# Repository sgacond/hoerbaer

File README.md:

# HörBär

## Idea
Build a more advanced, better sounding and better looking big brother of the commercially available [Hörbert](https://www.hoerbert.com/).

## Components
- A wonderful grand-father home made wooden housing. See: [C. Mosberger Restaurierung und Kunsthandwerk](http://www.cmosberger.ch/).
- MCU: ESP32
- PmodI2S DAC
- Adafruit MAX9744 based amplifier board
- Visaton FX 10 5" coaxial speaker

## Credits
Some of Neil Kolbans [CPP Utils](https://github.com/nkolban/esp32-snippets).  
Ideas and components from [ESP32_MP3_Decoder](https://github.com/MrBuddyCasino/ESP32_MP3_Decoder).  
Thank you!

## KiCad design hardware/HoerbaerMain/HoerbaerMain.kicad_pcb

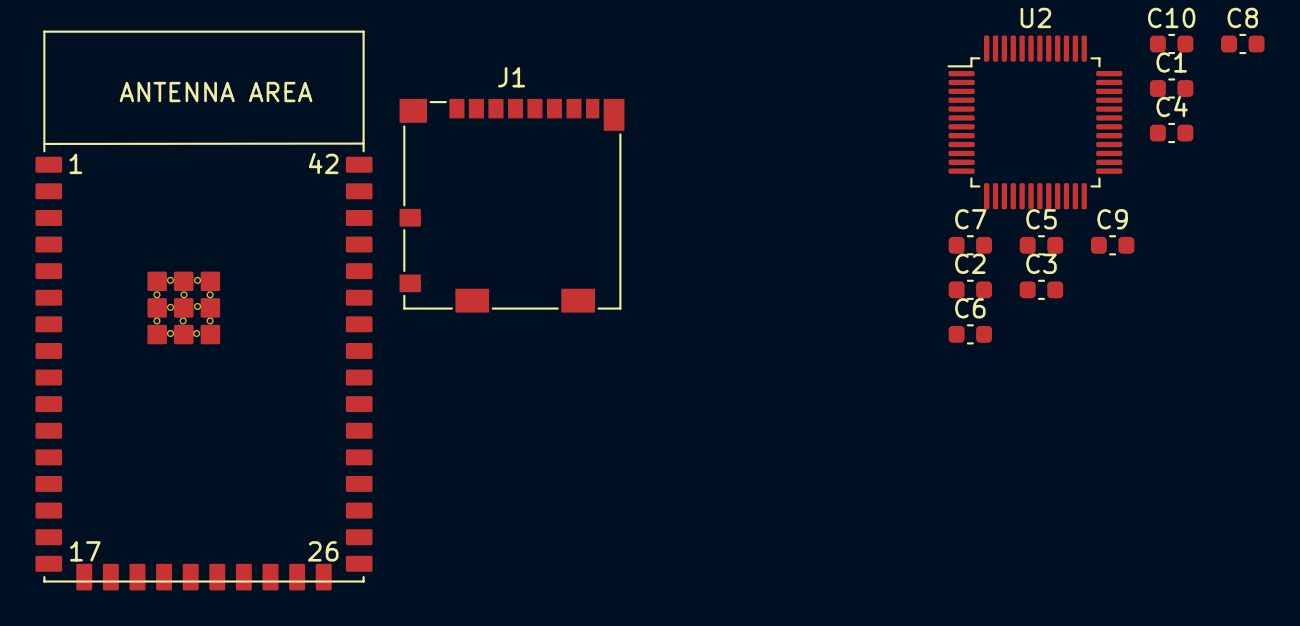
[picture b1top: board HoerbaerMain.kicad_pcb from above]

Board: 2 copper layers, 13 parts (0 on the bottom side), 3 nets, no tracks yet.

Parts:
C1, C2, C3, C4, C5, C6, C7, C8, C9, C10: 100nF; C_0603_1608Metric
J1: Micro_SD_Card; microSD_HC_Molex_104031-0811
U1: esp32-s2-wroom; esp32-s2-wrooom
U2: VS1053B; LQFP-48_7x7mm_P0.5mm

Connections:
GNDA: C1.2, C2.2, C3.2, U2.37 (AGND0), U2.40 (AGND1), U2.41 (AGND2), U2.47 (AGND3)
GNDD: C4.2, C5.2, C6.2, C7.2, C8.2, C9.2, C10.2, U2.4 (DGND0), U2.16 (DGND1), U2.20 (DGND2), U2.21 (DGND3), U2.22 (DGND4), U2.35 (GND)
VCC: C1.1, C2.1, C3.1, C4.1, C5.1, C6.1, C7.1, C8.1, C9.1, C10.1, U2.5 (CVDD0), U2.6 (IOVDD0), U2.7 (CVDD1), U2.14 (IOVDD1), U2.19 (IOVDD2), U2.24 (CVDD2), U2.31 (CVDD3), U2.38 (AVDD0), U2.43 (AVDD1), U2.45 (AVDD2)

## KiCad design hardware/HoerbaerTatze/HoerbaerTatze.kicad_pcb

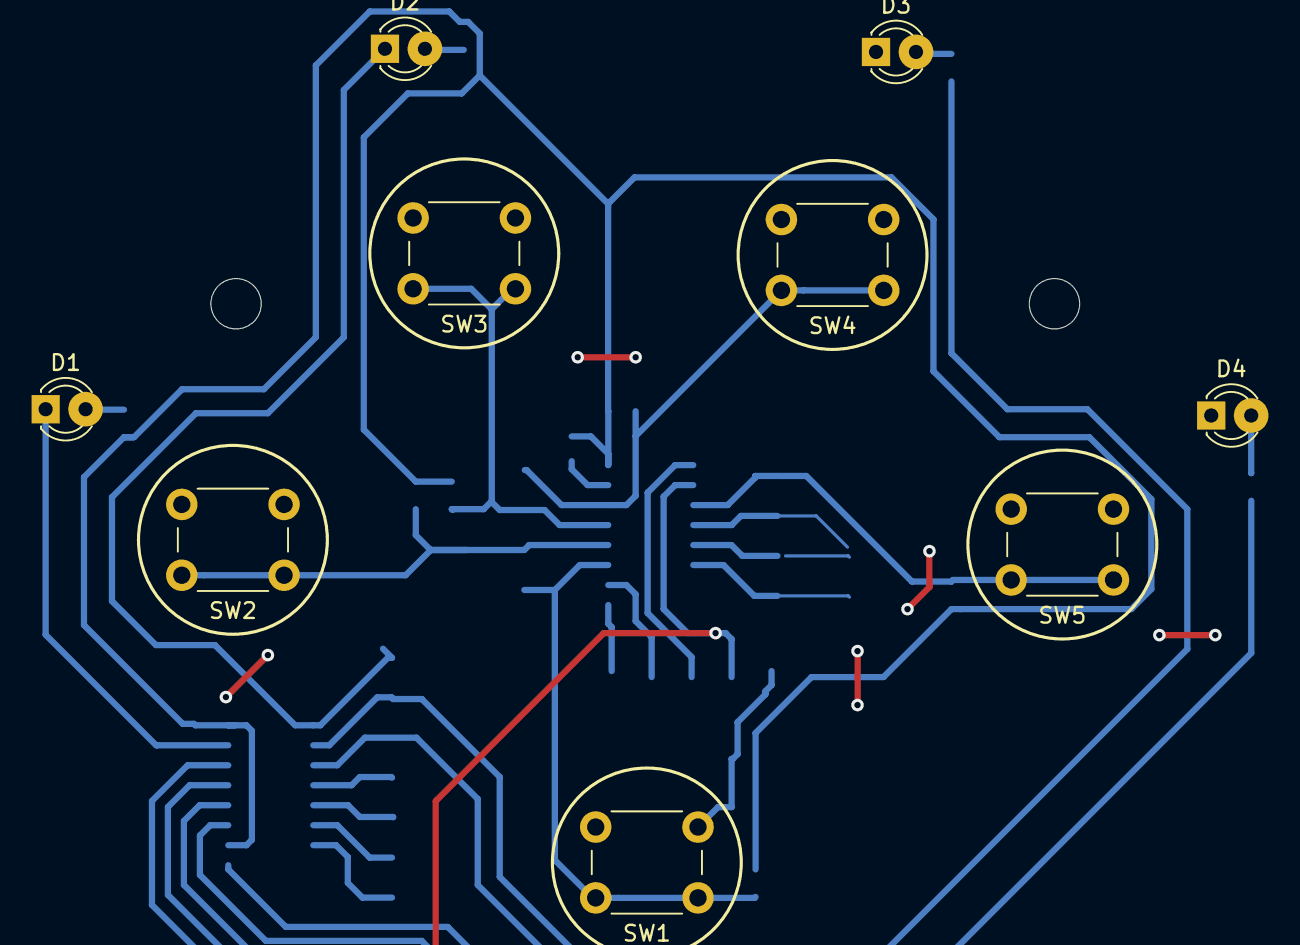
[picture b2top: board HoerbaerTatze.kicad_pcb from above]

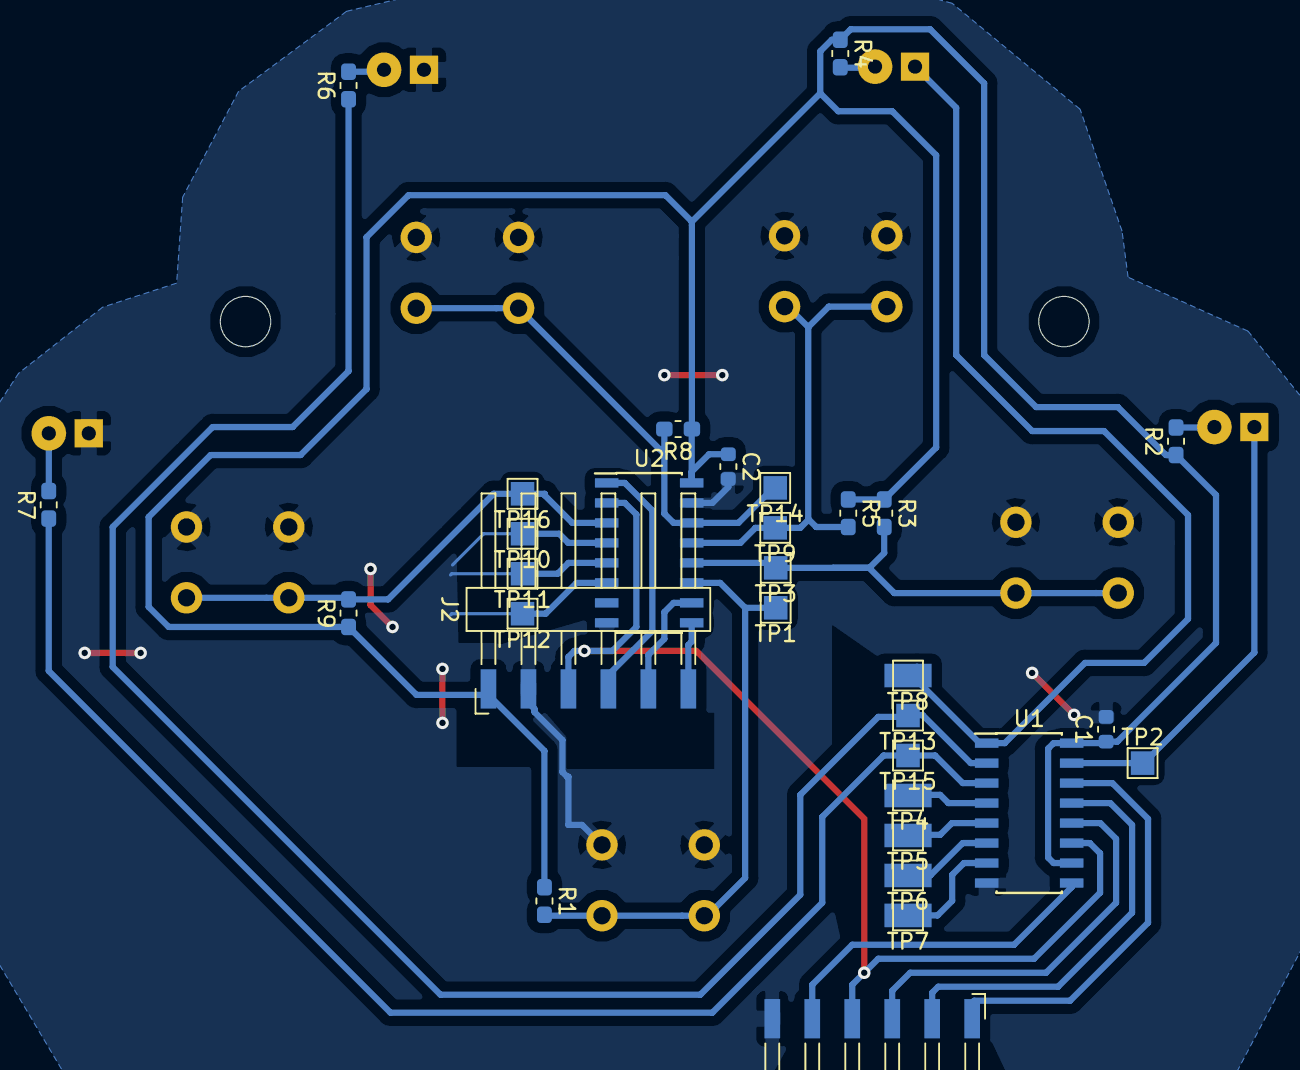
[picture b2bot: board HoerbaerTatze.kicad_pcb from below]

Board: 2 copper layers, 43 parts (31 on the bottom side), 27 nets.

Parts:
C1, C2: C; C_0603_1608Metric
D1, D2, D3, D4: LED; LED_D3.0mm
J1, J2: SWITCH; Harwin_M20-89006xx_1x06_P2.54mm_Horizontal
MH1, MH3, MH4: MountingHole; MountingHole_3.2mm_M3
R1, R3, R5, R8, R9: 10k; R_0603_1608Metric_Pad1.05x0.95mm_HandSolder
R2, R4, R6, R7: R; R_0603_1608Metric_Pad1.05x0.95mm_HandSolder
SW1, SW2, SW3, SW4, SW5: SW_Push; SW_PUSH_6mm
TP1, TP2, TP3, TP4, TP5, TP6, TP7, TP8, TP9, TP10, TP11, TP12, TP13, TP14, TP15, TP16: TestPoint; TestPoint_Pad_1.5x1.5mm
U1: 74HC595; SOIC-16_3.9x9.9mm_P1.27mm
U2: 74HC165; SOIC-16_3.9x9.9mm_P1.27mm

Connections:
CHAIN_SERIAL_IN: J2.5, U2.10
CHAIN_SERIAL_OUT: J1.5, U1.9
CLK: J1.4, J2.3, U1.11, U2.2
GND: C1.2, C2.2, D3.1, D4.1, J1.6, J2.2, SW1.1, SW2.1, SW3.1, SW4.1, SW5.1, TP10.1, TP11.1, TP12.1, U1.8, U2.4, U2.5, U2.6, U2.8, U2.15
IN_LATCH: J2.4, U2.1
LED1_LOW: D1.1, TP2.1, U1.15
LED2_LOW: D2.1, TP8.1, U1.1
LED3_HIGH: R6.1, TP13.1, U1.2
LED4_HIGH: R7.1, TP15.1, U1.3
LED_DIM_PWM: J1.2, U1.13
MISO: J2.6, U2.9
MOSI: J1.1, U1.14
unnamed: D1.2, R2.2
unnamed: D2.2, R4.2
unnamed: D3.2, R6.2
unnamed: D4.2, R7.2
unnamed: TP4.1, U1.4
unnamed: TP5.1, U1.5
unnamed: TP6.1, U1.6
unnamed: TP7.1, U1.7
OUT_LATCH: J1.3, U1.12
SW1: R1.2, SW1.2, TP1.1, U2.11
SW2: R3.2, SW2.2, TP3.1, U2.12
SW3: R5.2, SW3.2, TP9.1, U2.13
SW4: R8.2, SW4.2, TP14.1, U2.14
SW5: R9.2, SW5.2, TP16.1, U2.3
VCC: C1.1, C2.1, J2.1, R1.1, R2.1, R3.1, R4.1, R5.1, R8.1, R9.1, U1.10, U1.16, U2.16

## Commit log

2018-10-20 WIP: audio player.
2018-10-20 WIP: audio player
2018-10-22 Added better dynamic wave header parsing.
2018-10-22 Wip: audio, ...
2018-12-16 wip: firmware, ui prototype and boilerplate
2018-12-16 ignored vscode cpp browse db.
2018-12-18 Bear is talking - nose can adjust volume... Much to do!
2018-12-21 WIP: audio playing.
2018-12-23 WIP: playing, sleeping, pause, resume, ...
2018-12-24 File loading - fs reading, paw events, ...
2018-12-24 Eof -> to next song.
2018-12-26 Some fixes after successful christmas presentation to the client ;).
2018-12-26 GPIO15 amp fix, SPI CS was selected.
2018-12-26 Update readme.
2018-12-26 Added readme - added pictures.
2018-12-26 Updated readme and content.
2018-12-27 Added License and component license files.
2018-12-27 Modified Readme.
2019-07-19 Changed max volume (no technical reason ;))
2020-02-18 ESP_IDF update
2023-06-04 Try v5 update.
2023-06-04 Compilable on v3.3.6
2023-06-04 Released max volume
2025-06-24 Bump pbkdf2 from 3.0.17 to 3.1.3 in /webui
    Bumps [pbkdf2](https://github.com/crypto-browserify/pbkdf2) from 3.0.17 to 3.1.3.
    - [Changelog](https://github.com/browserify/pbkdf2/blob/master/CHANGELOG.md)
    - [Commits](https://github.com/crypto-browserify/pbkdf2/compare/v3.0.17...v3.1.3)
    ---
    updated-dependencies:
    - dependency-name: pbkdf2
2025-07-18 Bump on-headers and compression in /webui
    Bumps [on-headers](https://github.com/jshttp/on-headers) and [compression](https://github.com/expressjs/compression). These dependencies needed to be updated together.
    Updates `on-headers` from 1.0.1 to 1.1.0
    - [Release notes](https://github.com/jshttp/on-headers/releases)
    - [Changelog](https://github.com/jshttp/on-headers/blob/master/HISTORY.md)
    - [Commits](https://github.com/jshttp/on-headers/compare/v1.0.1...v1.1.0)
    Updates `compression` from 1.7.3 to 1.8.1
2025-08-06 Bump tmp and react-scripts in /webui
    Removes [tmp](https://github.com/raszi/node-tmp). It's no longer used after updating ancestor dependency [react-scripts](https://github.com/facebook/create-react-app/tree/HEAD/packages/react-scripts)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
    Removes `tmp`
    Updates `react-scripts` from 2.1.1 to 5.0.1
    - [Release notes](https://github.com/facebook/create-react-app/releases)
    - [Changelog](https://github.com/facebook/create-react-app/blob/main/CHANGELOG-2.x.md)
    - [Commits](https://github.com/facebook/create-react-app/commits/react-scripts@5.0.1/packages/react-scripts)
2025-08-20 Bump brace-expansion from 1.1.11 to 1.1.12 in /webui
    Bumps [brace-expansion](https://github.com/juliangruber/brace-expansion) from 1.1.11 to 1.1.12.
    - [Release notes](https://github.com/juliangruber/brace-expansion/releases)
    - [Commits](https://github.com/juliangruber/brace-expansion/compare/1.1.11...v1.1.12)
    ---
    updated-dependencies:
    - dependency-name: brace-expansion
2025-08-21 Bump cipher-base from 1.0.4 to 1.0.6 in /webui
    Bumps [cipher-base](https://github.com/crypto-browserify/cipher-base) from 1.0.4 to 1.0.6.
    - [Changelog](https://github.com/browserify/cipher-base/blob/master/CHANGELOG.md)
    - [Commits](https://github.com/crypto-browserify/cipher-base/compare/v1.0.4...v1.0.6)
    ---
    updated-dependencies:
    - dependency-name: cipher-base
2025-08-21 Bump sha.js from 2.4.11 to 2.4.12 in /webui
    Bumps [sha.js](https://github.com/crypto-browserify/sha.js) from 2.4.11 to 2.4.12.
    - [Changelog](https://github.com/browserify/sha.js/blob/master/CHANGELOG.md)
    - [Commits](https://github.com/crypto-browserify/sha.js/compare/v2.4.11...v2.4.12)
    ---
    updated-dependencies:
    - dependency-name: sha.js
2025-11-18 Bump js-yaml from 3.12.0 to 3.14.2 in /webui
    Bumps [js-yaml](https://github.com/nodeca/js-yaml) from 3.12.0 to 3.14.2.
    - [Changelog](https://github.com/nodeca/js-yaml/blob/master/CHANGELOG.md)
    - [Commits](https://github.com/nodeca/js-yaml/compare/3.12.0...3.14.2)
    ---
    updated-dependencies:
    - dependency-name: js-yaml
2025-11-27 Bump node-forge and react-scripts in /webui
    Bumps [node-forge](https://github.com/digitalbazaar/forge) to 1.3.2 and updates ancestor dependency [react-scripts](https://github.com/facebook/create-react-app/tree/HEAD/packages/react-scripts). The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
    Updates `node-forge` from 0.7.5 to 1.3.2
    - [Changelog](https://github.com/digitalbazaar/forge/blob/main/CHANGELOG.md)
    - [Commits](https://github.com/digitalbazaar/forge/compare/0.7.5...v1.3.2)
    Updates `react-scripts` from 2.1.1 to 5.0.1
    - [Release notes](https://github.com/facebook/create-react-app/releases)
2026-01-01 Bump qs and react-scripts in /webui
    Bumps [qs](https://github.com/ljharb/qs) to 6.14.1 and updates ancestor dependency [react-scripts](https://github.com/facebook/create-react-app/tree/HEAD/packages/react-scripts). These dependencies n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
    Updates `qs` from 6.5.2 to 6.14.1
    - [Changelog](https://github.com/ljharb/qs/blob/main/CHANGELOG.md)
    - [Commits](https://github.com/ljharb/qs/compare/v6.5.2...v6.14.1)
    Updates `react-scripts` from 2.1.1 to 5.0.1
    - [Release notes](https://github.com/facebook/create-react-app/releases)
2026-01-15 Bump diff and react-scripts in /webui
    Removes [diff](https://github.com/kpdecker/jsdiff). It's no longer used after updating ancestor dependency [react-scripts](https://github.com/facebook/create-react-app/tree/HEAD/packages/react-script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
    Removes `diff`
    Updates `react-scripts` from 2.1.1 to 5.0.1
    - [Release notes](https://github.com/facebook/create-react-app/releases)
    - [Changelog](https://github.com/facebook/create-react-app/blob/main/CHANGELOG-2.x.md)
    - [Commits](https://github.com/facebook/create-react-app/commits/react-scripts@5.0.1/packages/react-scripts)
2026-01-17 Bump tar and react-scripts in /webui
    Removes [tar](https://github.com/isaacs/node-tar). It's no longer used after updating ancestor dependency [react-scripts](https://github.com/facebook/create-react-app/tree/HEAD/packages/react-scripts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
    Removes `tar`
    Updates `react-scripts` from 2.1.1 to 5.0.1
    - [Release notes](https://github.com/facebook/create-react-app/releases)
    - [Changelog](https://github.com/facebook/create-react-app/blob/main/CHANGELOG-2.x.md)
    - [Commits](https://github.com/facebook/create-react-app/commits/react-scripts@5.0.1/packages/react-scripts)
2026-01-24 Bump lodash from 4.17.11 to 4.17.23 in /webui
    Bumps [lodash](https://github.com/lodash/lodash) from 4.17.11 to 4.17.23.
    - [Release notes](https://github.com/lodash/lodash/releases)
    - [Commits](https://github.com/lodash/lodash/compare/4.17.11...4.17.23)
    ---
    updated-dependencies:
    - dependency-name: lodash
2026-01-30 Bump diff from 3.5.0 to 3.5.1 in /webui
    Bumps [diff](https://github.com/kpdecker/jsdiff) from 3.5.0 to 3.5.1.
    - [Changelog](https://github.com/kpdecker/jsdiff/blob/master/release-notes.md)
    - [Commits](https://github.com/kpdecker/jsdiff/compare/v3.5.0...v3.5.1)
    ---
    updated-dependencies:
    - dependency-name: diff
2026-02-03 Bump url-parse from 1.4.4 to 1.5.10 in /webui
    Bumps [url-parse](https://github.com/unshiftio/url-parse) from 1.4.4 to 1.5.10.
    - [Commits](https://github.com/unshiftio/url-parse/compare/1.4.4...1.5.10)
    ---
    updated-dependencies:
    - dependency-name: url-parse
    dependency-version: 1.5.10
2026-02-04 Bump semver in /webui
    Bumps and [semver](https://github.com/npm/node-semver). These dependencies needed to be updated together.
    Updates `semver` from 5.6.0 to 5.7.2
    - [Release notes](https://github.com/npm/node-semver/releases)
    - [Changelog](https://github.com/npm/node-semver/blob/v5.7.2/CHANGELOG.md)
    - [Commits](https://github.com/npm/node-semver/compare/v5.6.0...v5.7.2)
    Updates `semver` from 5.5.0 to 5.5.0
